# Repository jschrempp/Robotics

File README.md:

# Robotics
Hardware, firmware, software and documentation for low cost robotics experimentation and development using 
Particle Photon and MIT App Inventor 2.

## Story
We (Team Practical Projects) wanted to explore the capabilities and limitations of very inexpensive robot 
technology.  We obtained a basic robot kit for about $12.  This kit contains a plastic chassis, two drive
motors and drive wheels, a front caster wheel, a 4 AA cell battery holder, an on/off switch, and mounting
and assembly hardware.  

In order to run, test and explore the robot, we designed and built a Particle Photon-based printed circuit
board.  We chose the Particle Photon for our microcontroller because of Arduino
code compatibility, the ability to flash new firmware over WiFi, and Particle's IoT cloud functionality.
However, we used an inexpensive bluetooth module for basic communication with the robot (vs. the Particle Cloud)
because we wanted to experiment with our robot both indoors and outdoors; the latter where there is no
WiFi available.

The printed circuit board that we designed for this project contains all of the electronics needed to control
and monitor the robot.  This board includes:
1. The Particle Photon.
2. A buck power converter (so that the electronics can be powered from the robot's batteries).
3. Interface circuitry for three HC-SR04 ultrasonic distance sensors.
4. An HC-05 bluetooth module.
5. A dual H-bridge motor controller capable of driving the two motors on the robot.
6. Expansion capability for future development.

We wrote an Android app (in MIT App Inventor 2) to communicate with the robot and control its motion
manually and in an automatic, self-navigating, obstacle-avoiding mode.  

This repository contains complete, open source documention for building and operating this robot.

## Findings
1. The cheap caster wheel that came with the robot kit had a tendency to bind up and send the robot off
at odd angles.  Our solution was to find a suitable ball caster that replaces the robot kit front wheel.

2. In order for the robot to self-navigate, it needs to take distance measurements to obstacles both in
front of the robot and on both sides of the robot.  We tried using a single ultrasonic sensor mounted on a servo but
we found that the overall measurment cycle was too slow for our purposes.  We opted for using three, fixed
mounted ultrasonic distance sensors: one in front and two facing to each side of the robot.  These sensors
are cheap enough for us to use them this way. The side sensors are needed in the event that the robot approaches 
a side wall at a heavily oblique angle.  In particular, we have found that these sensors should face the 
side somewhere between 60 degrees and 90 degrees from the robot's front. We were unable to determine a single 
optimal angle for the side avoidance sensors.  We believe that there is too much dependancy on wall reflectivity 
and corner angles to establish a single, best sensor configuration (owning, we believe, to multi-path effects -- see below).

3. We found that there are dead spots between the three ultrasonic sensors. If the robot approaches an obstacle in 
the dead spot (e.g. a table leg), it will get hung up. We also found that the ultrasonic sensors are subject to multi-path effects.  The
ultrasonic signals can bounce off of multiple walls before returning to the sensor, resulting in incorrect distance measurements.
We also found that it is possible for a multi-path signal reflection from one sensor to be detected by another
sensor.  We created a delay of 1 millisecond between sensor readings in order to reduce this effect.  

4. We found that different surfaces reflect different amounts of ultrasonic energy.  Some surfaces (generally
soft surfaces) are poor reflectors of ultrasonic signals while other surfaces (generally hard surfaces) perform much better.
Unsurprisingly, the robot works best when tested against hard vertical walls set at right angles to each other.

5. Given the limitations of ultrasonic distance sensors, we investigated alternatives but we were unable to find
any suitable alternative sensors in the low cost range.  We tried infrared distance sensors that work by measuring
the strength of reflected infrared energy, but we found that the performance was highly sensitive to the color
of a surface.  White walls worked well, whereas black walls did not work at all (absorbed almost all of the
infrared energy).  We concluded that the best sensor technology would likely be lidar, but the cost of lidar
technology far exceeds the cost constriants of this project.

6. We found that weight distribution on the robot body impacts robot traction. The heaviest item on the 
robot platform are the batteries.  It would be best to place the battery holder directly over axis between
the two rear drive wheels. However, the parts don't fit well in this configuration.  The parts fit best
in the conguration shown on the photo "Robot.png" in this repository; however, traction is not
optimal with this configuration of parts.  Traction is improved by placing the printed circuit board
up front and the battery holder in the back.

7. The overall ability of the robot to self-navigate and avoid obstacles is fairly impressive, given the
limitations of the sensing capability.  The robot has the ability to find a way out from most obstacles,
including corners, chair and table legs, etc. Self navigation is not perfect, however.
The robot pivots on an axis between the rear drive wheels and not the center of the chassis, which results
in the pivot arc being longer than we had expected.  A 4 wheel
robot or a robot based on a tank chassis might obviate this problem.  Alternatively, adding a rear sensor and
firmware to back the robot out of a jam (in lieu of pivoting the robot to move out of a jam forward) might
improve this behavior.

8. The strength of the motors and the size of the drive and caster wheels limit the types of surfaces where the robot
can operate successfully.  A flat hard surface or a very low pile office carpet work well.  Plush carpet and 
height transitions do not work well with this robot. A tank chassis might allow the robot to operate over
small height transitions and on plush surfaces.

We have documented the robot's behavior in autonomous navigation mode (AUTO) in a series of six videos that 
you can view, beginning here:

https://www.youtube.com/watch?v=S9v4ddf_cKs&list=PLz4TQp3CqyALdgTUBRFCJkOn_9tXRT2St

In addition to autonomous mode, the Robot can be manually steered via the app supplied with this project.

## Conclusions
Our conclusion is that the robot can successfully navigate autonomously over a fairly wide range of challenging
conditions, given the limitations of the low cost hardware used.

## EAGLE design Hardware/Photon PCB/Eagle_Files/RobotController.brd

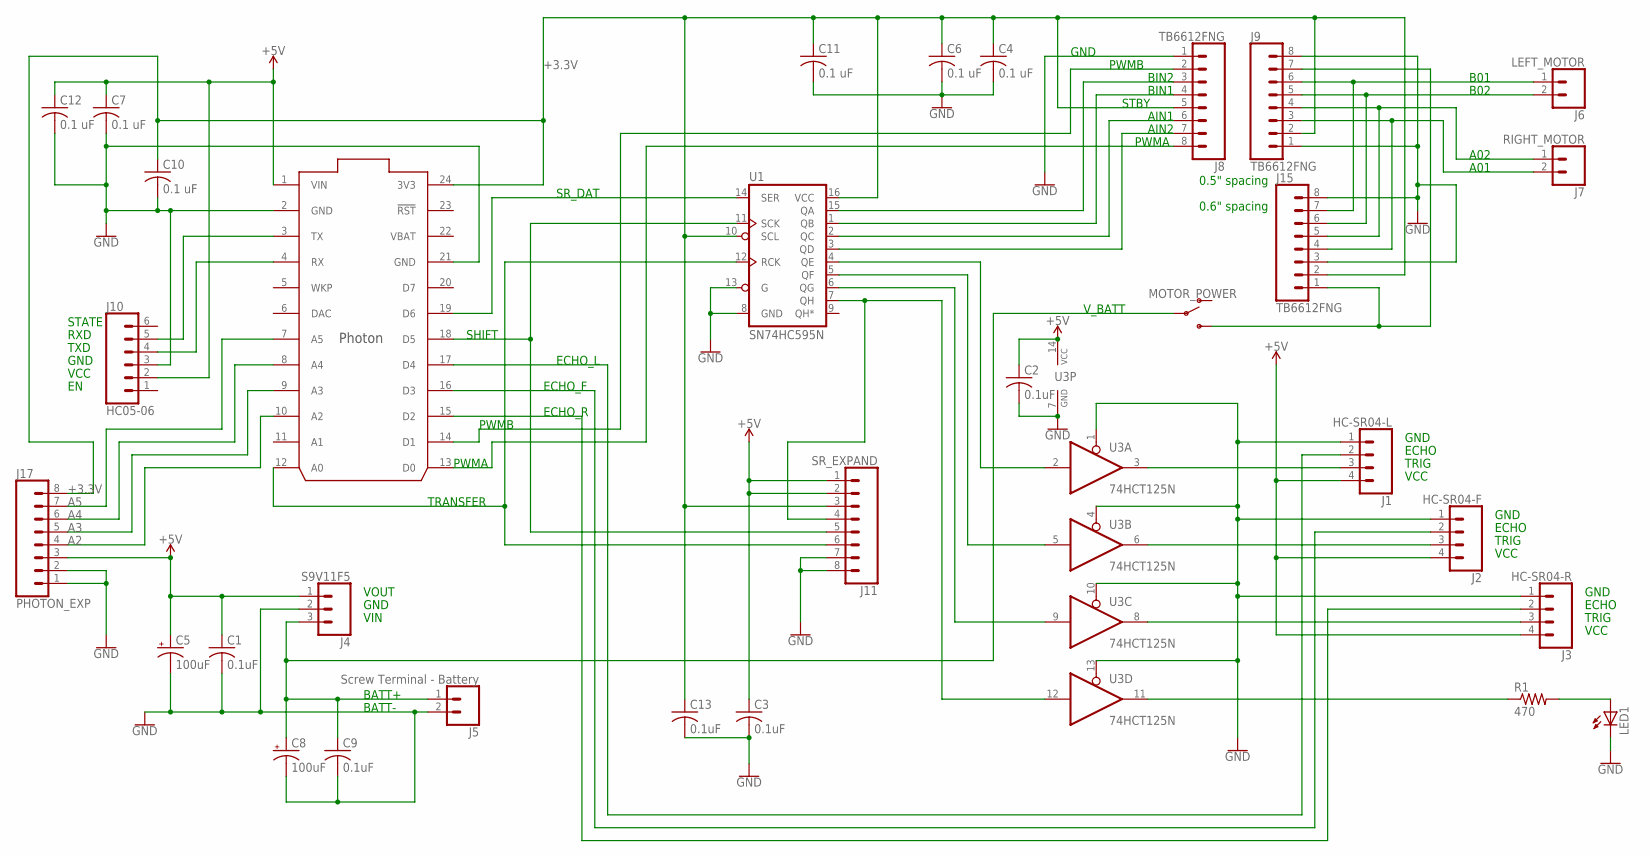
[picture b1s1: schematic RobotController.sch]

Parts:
C1, C2, C3, C9, C13: 0.1uF; C025-024X044
C4, C6, C7, C10, C11, C12: 0.1 uF; C025-024X044
C5, C8: 100uF; E2,5-6E
J1: HC-SR04-L; 1X04
J2: HC-SR04-F; 1X04
J3: HC-SR04-R; 1X04
J4: S9V11F5; 1X03
J5: Screw Terminal - Battery; SCREWTERMINAL-3.5MM-2
J6: LEFT_MOTOR; SCREWTERMINAL-3.5MM-2
J7: RIGHT_MOTOR; SCREWTERMINAL-3.5MM-2
J8, J9, J15: TB6612FNG; 1X08
J10: HC05-06; 1X06
J11: SR_EXPAND; 1X08
J17: PHOTON_EXP; 1X08
LED1: LED5MM
MOTOR_POWER: SWITCH-SPDT-PTH-11.6X4.0MM; SWITCH_SPDT_PTH_11.6X4.0MM
R1: 470; 0207/10
U1: SN74HC595N; DIP16
U3: 74HCT125N; DIL14
U$1: PHOTON_WITH_HEADERS; PHOTON

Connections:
+3.3V: C4.1, C6.1, C10.1, C11.1, C13.1, J8.5, J9.2, J11.3, J15.2, J17.8, U1.10 (SCL), U1.16 (VCC), U$1.24 (3V3)
A2: J17.4, U$1.10 (A2)
A3: J17.5, U$1.9 (A3)
A4: J17.6, U$1.8 (A4)
A5: J17.7, U$1.7 (A5)
GND: C1.2, C2.2, C3.2, C4.2, C5.-, C6.2, C7.2, C8.-, C9.2, C10.2, C11.2, C12.2, C13.2, J1.1, J2.1, J3.1, J4.2, J5.2, J8.1, J9.1, J9.8, J10.3, J11.7, J11.8, J15.3, J15.8, J17.1, J17.2, LED1.K (C), U1.8 (GND), U1.13 (G), U3.1 (OE), U3.4 (OE), U3.7 (GND), U3.10 (OE), U3.13 (OE), U$1.2 (GND), U$1.21 (GND)
unnamed: U1.14 (SER), U$1.19 (D6)
unnamed: J11.6, U1.12 (RCK), U$1.12 (A0)
unnamed: J11.4, U1.7 (QH), U3.12 (I)
unnamed: U1.4 (QE), U3.2 (I)
unnamed: U1.5 (QF), U3.5 (I)
unnamed: U1.6 (QG), U3.9 (I)
unnamed: J9.7, J15.1, MOTOR_POWER.3 (S)
unnamed: J11.5, U1.11 (SCK), U$1.18 (D5)
unnamed: C8.+, C9.1, J4.3, J5.1, MOTOR_POWER.2
unnamed: J1.3, U3.3 (O)
unnamed: J2.3, U3.6 (O)
unnamed: J3.3, U3.8 (O)
unnamed: R1.1, U3.11 (O)
unnamed: LED1.A, R1.2
unnamed: J7.2, J9.3, J15.4
unnamed: J7.1, J9.4, J15.5
unnamed: J6.2, J9.5, J15.6
unnamed: J6.1, J9.6, J15.7
unnamed: J2.2, U$1.16 (D3)
unnamed: J8.3, U1.15 (QA)
unnamed: J3.2, U$1.15 (D2)
unnamed: J8.4, U1.1 (QB)
unnamed: J8.6, U1.2 (QC)
unnamed: J8.7, U1.3 (QD)
unnamed: J1.2, U$1.17 (D4)
unnamed: J8.2, U$1.14 (D1)
unnamed: J8.8, U$1.13 (D0)
unnamed: J10.5, U$1.3 (TX)
unnamed: J10.4, U$1.4 (RX)
VBAT: U$1.22 (VBAT)
VCC: C1.1, C2.1, C3.1, C5.+, C7.1, C12.1, J1.4, J2.4, J3.4, J4.1, J10.2, J11.1, J11.2, J17.3, U3.14 (VCC), U$1.1 (VIN)

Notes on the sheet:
VIN
GND
VOUT
BATT+
BATT-
ECHO
TRIG
VCC
V_BATT
PWMA
PWMB
STBY
BIN1
BIN2
AIN2
AIN1
B01
B02
A02
A01
0.5" spacing
SHIFT
TRANSFER
SR_DAT
ECHO_L
ECHO_F
ECHO_R
TXD
RXD
STATE
0.6" spacing

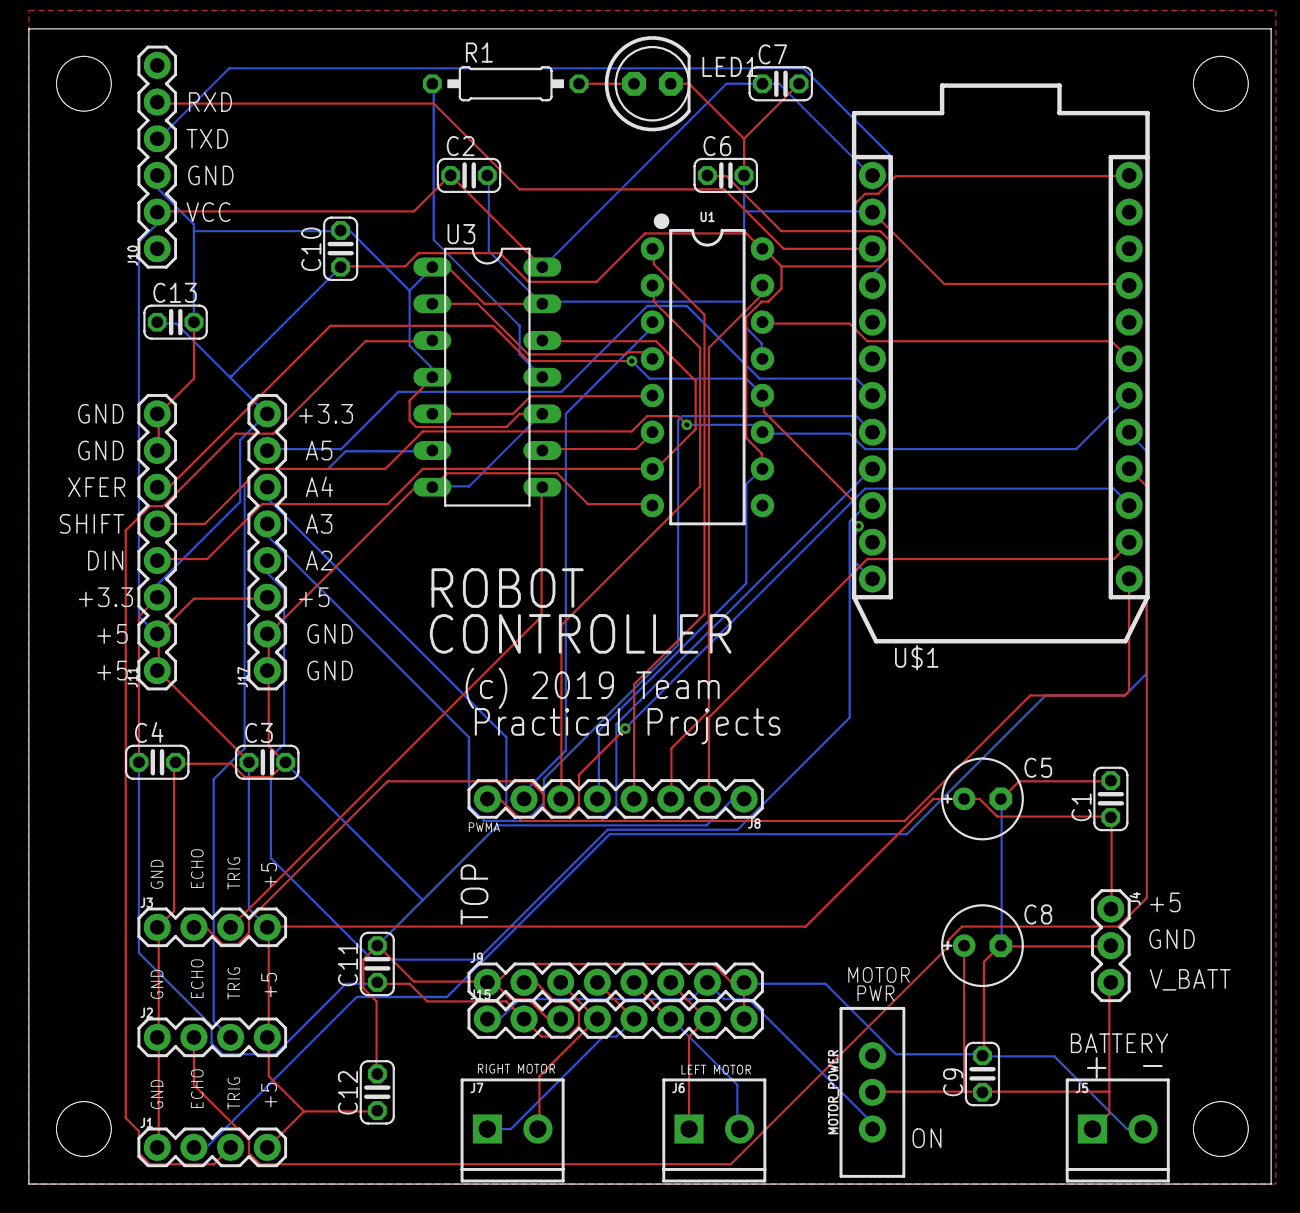
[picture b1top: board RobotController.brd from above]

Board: 2 copper layers, 86.0 x 80.0 mm, 32 parts (0 on the bottom side), 36 nets.

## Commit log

2018-11-03 Initial commit of test project data
    Created test and Development folder and subfolders for bluetooth and
    ultrasonic sensor testing. Uploaded hardware, software and descriptive
    text to each sub folder, as required.
2018-11-03 Minor edits to ReadMe
2018-11-03 Added ReadMe for the Ultrasonic Sensor test
2018-11-03 deleted temp file
2018-11-05 Added firmware and app code to send data
    Messages are sent from the Arduino to the app over bluetooth in response
    to commands to change the LED state. The app polls for received
    bluetooth data on a 1 second timer and reds and displays the data
    accordingly.
2018-11-12 Added motor control schematic
2018-11-12 Added test firmware version 1.0
2018-11-13 Added datasheets for motor driver module
2018-11-13 Completed test firmware
    implemented and test high and low speed forward and backward motion plus
    stop and brake functionality.
2018-11-13 Added ReadMe file
    Description of what is in this folder.
2018-11-13 Corrected minor ReadMe errors.
2018-11-13 Added CAD file
    Added a Hardware folder and the laser cutter CAD file for the
    electronics platform.
2018-11-14 Added robot assembly instructions
    Added scan of robot manufacturer's assembly instructions. Added some
    folders for organizational purposes.
2018-11-16 Initial release of the Robot Control project
    App and documentation to be supplied.
2018-11-17 Basic Robot Control App
    Created and documented a basic robot control app and associated robot
    hardware and firmware.
2018-11-17 Perforrmance tuning
    Change high and low speed constants to make the robot more responsive.
2018-11-22 Version 1.1
    Slightly altered the low speed and turn constants to make the robot more
    controllable from the app.
2018-11-29 Added sweep distance test
    Added code to test out the ultrasonic rangefinder mounted on a servo at
    the front of the robot. Test to calibrate the sweep delay time to give
    accurate and repeatable distance results.
2018-11-30 Changed BT Rx pin for Yun compatibility
    Changed the robot firmware and BT test firmware to use pin 10 for
    received serial data for Yun/Leonardo compatibility. Also edited the
    returned messages for BT commands to make them more meaningful. Made
    defined constants for BT TX and Rx pins. Likewise, changed the BT
    serial pins on the BT test firmware and also made changes on the
    schematic diagrams to reflect this pin change.
2018-11-30 Updated pin assignments in ReadMe file
2018-12-02 Integrated rangefinder and robot control code
    Just basic forward and detect obstical and stop functionality for now.
    Need to add sweep and decision about turns after basic testing and
    observation of robot movement.
2018-12-02 Fixed bug
2018-12-02 Changes minimum distance to stop after testing
2018-12-02 App now supports selection of autonomous mode
2018-12-02 Updated ReadMe with current project status.
2018-12-08 Autonomous firmare
    Updated firmware to version 1.1 featuring autonomous operation of the
    robot. If the robot encounters an obstacle ahead, it randomly chooses a
    direction to pivot. The robot pivots in that direction and measures
    distance ahead until either finds an open pathway to proceed forward or
    else it gives up ("stuck") and defaults back to the manual mode. Readme
    has been updated accordingly.
2018-12-09 Eliminated the servo
    The servo fell off in testing, so I took it out of the hardware and the
    code altogether. I also cleaned up the code and readme.
2018-12-09 Minor cleanup - no functional changes
2018-12-21 Updated firmware and ReadMe
    Added left and right side ultrasonic sensors at 45 degree angles off of
    front and updated firware to process these sensor in order to avoid the
    robot hitting a wall obliquely. Updated readMe accordingly.
2018-12-21 Added photo of 3 sensor robot
2018-12-23 Revert "Added photo of 3 sensor robot"
    This reverts commit 8b5abbcf5b6712b8ba0c0cd571c21a58c1b55ae2.
2018-12-23 Firmware v1.5
    Firmware version 1.5 includes a timeout on pulseIn() so that rangefinder
    measurements are terminated after 20 ms (about 11 feet) and distance is
    set to 20 ms (11 feet). This is so that the robot does not move too
    much while blocked by measurement times.
2018-12-23 Added photo of robot to Hardware folder
2018-12-31 pulled button color changes into one procedure
2018-12-31 display disconnect in red whenever the bluetooth connection is found to be down.
2019-01-02 app reports distances when in autonomous mode
2019-01-11 Version 2.0 firmware and app code
    Version 2.0 fixes the distance reporting function bug in the app. It
    also updates the inline comments and version on the firmware and version
    number of the app to both reflect version 2.0.
2019-01-16 restructured avoidance code
2019-01-17 moved distance variables back out of globals and into mainloop
2019-01-18 restructure of measuredistance function. no change to functionality
2019-01-19 v2.2 restores random direction and five pivots
2019-01-19 v2.3 Now check side only if ahead is clear. Also, always sense distance after a movement; don't make avoidance decisions with stale distance data.
2019-01-22 added 3ms delay after each sonic sense. eliminated ghost avoidance
2019-01-23 removed 3ms delay. reset forward pivot count when side avoidance happens.
2019-01-24 Updated comments for version 2.5
    Updated the comments to show the latest changes, including removal of 3
    ms delays between measurements and adding reset of numPivots in the
    event that the path was clear but a side is obstructed.
2019-01-30 Added three front behavior: close, near, clear. And two side: close, near. Added smooth pivot when near. v2.5
2019-04-12 Photon Controller Hardware Test
    Schematic for Photon Controller breadboard hardware test posted. Photon code posted that integrates bluetooth and motor control; but not yet shift registers or US integration.
2019-04-13 Motor Test
    Added a motor control test that uses the shift register to control motor function/direction, as per the schematic. The motor control test is based upon a similar test routine for the Arduino Uno vers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
2019-04-15 Create Photon_Robot_US-test.ino
    This test routine tests out three HC-SR04 ultrasound modules whose triggers are via the shift register and echo pins go to 5v tolerant inputs on the Photon. A new reading is taken from a sensor and p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
2019-04-22 Update RobotController.pdf
    Added wiring for larger motor controller module and connectors for spare SR and spare Photon pins.
2019-04-24 Update RobotController.pdf
    Reduced schematic to one SR and one level converter in order to reduce board area. Added expansion connectors.
2019-05-02 Completed PCB
    I added the Eagle schematic and board files for the completed (v1) PCB.
2019-05-05 Create Robot Controller PCB Parts List.xlsx
    Preliminary parts list for the Robot Controller PCB. This parts list only contains parts on the PCB. It does not contain external robot parts: robot body, motors, batteries/holder, ultrasonic modules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
2020-08-22 Create AutonomousRobotParticle.ino
    This is the Photon version of the earlier Arduino code. It supports the Photon based hardware configuration of the Robot PCB circuit. Funtionality is identical to the previous Arduino version.
2020-08-22 Photon Robot HW and FW
    Photon PCB based robot photos, parts list, Schematic, Eagle Files, and Firmware added to this repository.
2020-08-23 Update AutonomousRobotParticle.ino
    Added system mode semi-automatic so that robot works if there is no wifi.
2020-08-25 Update AutonomousRobotParticle.ino
    Added in version of pulseIn() with timeout that I found on the Particle Community. Modified code accordingly and tested.
2020-08-26 Latest version of AI2 App
    It wasn't clear that the version of the AI2 app checked in here is the latest, including formatting of distance measurement display. The late4st app is now here.
2020-08-30 set up for visual studio code
2020-08-30 removed old file locations
2020-08-31 v 3.3 glide past side obstacles
2020-09-03 3.4 grounding A2 causes WiFi connect
2020-09-03 correction to disable default Autonomous mode
2020-09-03 Now compiles without warnings
2020-09-03 Cloud function to assert Autonomous mode
2020-09-05 blink LED on each measurement cycle
2020-09-06 Cleaned up and Added Parts List
    Cleaned up this repository with the PCB version. Updated the PCB Parts List and added a Robot overall parts list. Parts lists are now in PDF format.
2020-09-07 added TOU document and updated README.md
2020-09-11 3.5x spin for avoid
2020-09-12 added comments
2020-09-13 Added manufacturer robot assy instructions
2020-09-14 added Documents folder
    Added documents folder and Build Instructions.
2020-09-14 First draft build instructions
2020-09-14 document placeholders
2020-09-16 Posted first draft of User Manual
2020-09-17 Removed legacy test code.
    Much of this development and test code was for the Arduino breadboard and not for general publication.
2020-09-17 Completed first draft of repository
    PDF versions are all documents are present.
2020-09-17 3.5x2 no BT delay
2020-09-18 debug is scrollable?
2020-09-24 3.6 new auto strategy
2020-09-24 bug caused oscillation
2020-09-25 front avoid is now random direction
2020-09-25 cleaned up lines, comments
2020-09-29 3.7 Remember pivot direction
2020-10-08 Updated docs
    Updated release copies of docs after review and after changing app photos to the latest app version
2020-10-08 Update Robot_User_Manual.pdf
    Updated with the latest App photos and debug description.
2020-10-09 Finalized Docs and Updated Readme.md
2020-10-13 Update AutonomousRobotParticle.ino
    Changed defined constants TOO_CLOSE_SIDE to 6.0 and NEAR_SIDE to 8.0 (added 2" to each). Intent is to see if chair leg avoidance is improved.
2020-10-16 3.10 to get it avoiding again
2020-11-02 3.11 front blocked limit
2020-11-04 3.12 front blocked is milliseconds
2020-11-04 android app reports all robot messages
2020-11-04 3.13 clean up
2020-11-08 new sensor test folder
2020-11-09 3.14 delay in measurements
2020-12-03 3.14 pivot more when forward blocked
2020-12-11 3.16 avoid front mode pivots significantly
2020-12-18 Update README.md
    Including the latest findings.
2020-12-18 after testing changes to make it work well

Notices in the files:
Hardware/Photon PCB/Eagle_Files/RobotController.brd:
(c) 2019 Team
parts and their libraries:
Particle-Devices: Licensing: Designed by Particle.
SparkFun-IC-Logic: Licensing: Creative Commons ShareAlike 4.0 International - https://creativecommons.org/licenses/by-sa/4.0
